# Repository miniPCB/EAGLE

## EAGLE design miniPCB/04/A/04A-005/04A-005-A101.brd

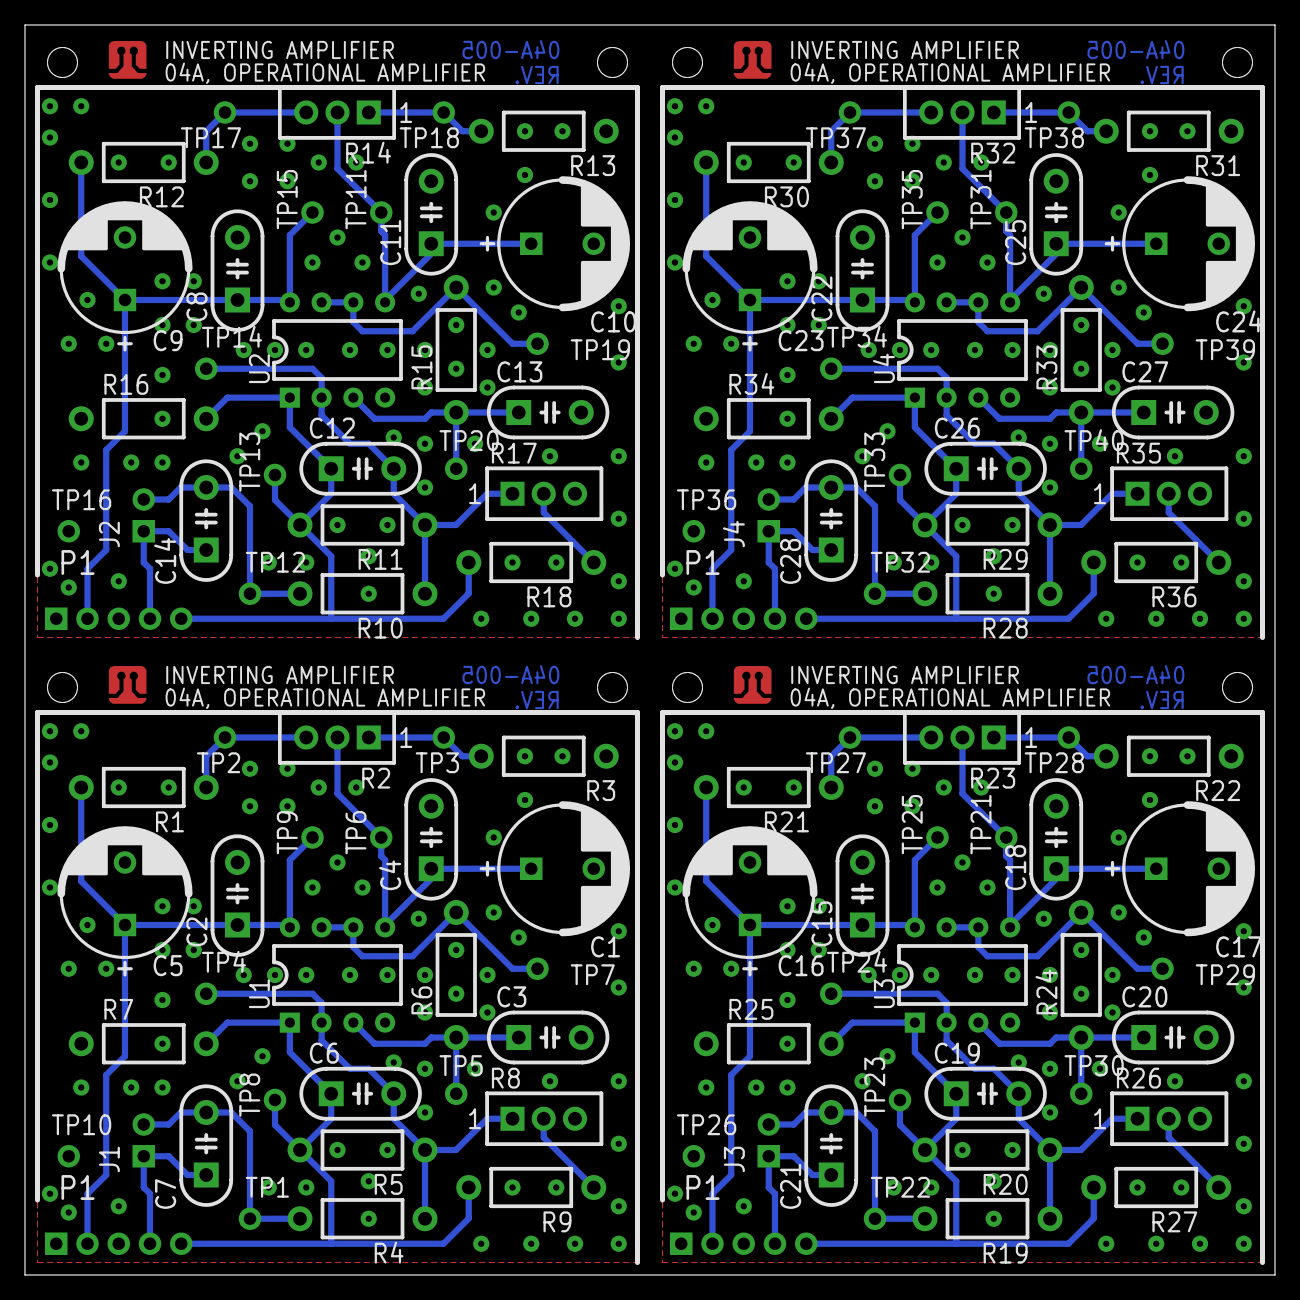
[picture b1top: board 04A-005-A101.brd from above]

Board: 2 copper layers, 100.0 x 100.0 mm, 120 parts (0 on the bottom side), 48 nets.

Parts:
C1, C5, C9, C10, C16, C17, C23, C24: C5MM
C2, C3, C4, C6, C7, C8, C11, C12, C13, C14, C15, C18, C19, C20, C21, C22, C25, C26, C27, C28: C050-024X044
J1, J2, J3, J4: JUMPER; PINS_2
P1, P2, P3, P4: PINS_1X5
R1, R3, R4, R5, R6, R7, R9, R10, R11, R12, R13, R15, R16, R18, R19, R20, R21, R22, R24, R25, R27, R28, R29, R30, R31, R33, R34, R36: 0207/10
R2, R8, R14, R17, R23, R26, R32, R35: TRIM_0100
TP1, TP2, TP3, TP4, TP5, TP6, TP7, TP8, TP9, TP10, TP11, TP12, TP13, TP14, TP15, TP16, TP17, TP18, TP19, TP20, TP21, TP22, TP23, TP24, TP25, TP26, TP27, TP28, TP29, TP30, TP31, TP32, TP33, TP34, TP35, TP36, TP37, TP38, TP39, TP40: PINS_1_TESTPOINT_KE5000_NOTEXT
U1, U2, U3, U4: DIL08
U$1, U$2, U$3, U$4: MINIPCB_50X50; MINIPCB_0P_50X50MM

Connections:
GND: C1.-, C2.2, C3.2, C4.2, C5.-, P1.1, R3.1, R7.1, TP10.1, U1.4
GND1: C8.2, C9.-, C10.-, C11.2, C13.2, P2.1, R13.1, R16.1, TP16.1, U2.4
GND2: C15.2, C16.-, C17.-, C18.2, C20.2, P3.1, R22.1, R25.1, TP26.1, U3.4
GND3: C22.2, C23.-, C24.-, C25.2, C27.2, P4.1, R31.1, R34.1, TP36.1, U4.4
IN: C7.1, J1.1, P1.4
IN1: C14.1, J2.1, P2.4
IN2: C21.1, J3.1, P3.4
IN3: C28.1, J4.1, P4.4
IN-DC: C7.2, J1.2, R4.2, TP1.1
IN-DC1: C14.2, J2.2, R10.2, TP12.1
IN-DC2: C21.2, J3.2, R19.2, TP22.1
IN-DC3: C28.2, J4.2, R28.2, TP32.1
unnamed: R8.2, R9.1
unnamed: R17.2, R18.1
unnamed: R26.2, R27.1
unnamed: R35.2, R36.1
OUT: C6.1, P1.5, R5.2, R7.2, R9.2, TP8.1, U1.1
OUT1: C12.1, P2.5, R11.2, R16.2, R18.2, TP13.1, U2.1
OUT2: C19.1, P3.5, R20.2, R25.2, R27.2, TP23.1, U3.1
OUT3: C26.1, P4.5, R29.2, R34.2, R36.2, TP33.1, U4.1
P1.1: R2.1, R3.2, TP3.1
P1.2: R12.1, R14.3, TP17.1
P1.3: R1.1, R2.3, TP2.1
P1.4: R13.2, R14.1, TP18.1
P1.5: R21.1, R23.3, TP27.1
P1.6: R22.2, R23.1, TP28.1
P1.7: R30.1, R32.3, TP37.1
P1.8: R31.2, R32.1, TP38.1
V+: C2.1, C5.+, P1.2, R1.2, TP9.1, U1.8
V+1: C8.1, C9.+, P2.2, R12.2, TP15.1, U2.8
V+2: C15.1, C16.+, P3.2, R21.2, TP25.1, U3.8
V+3: C22.1, C23.+, P4.2, R30.2, TP35.1, U4.8
VFB: C6.2, R4.1, R5.1, R8.1, TP4.1, U1.2
VFB1: C12.2, R10.1, R11.1, R17.1, TP14.1, U2.2
VFB2: C19.2, R19.1, R20.1, R26.1, TP24.1, U3.2
VFB3: C26.2, R28.1, R29.1, R35.1, TP34.1, U4.2
VR: C1.+, C4.1, R2.2, TP6.1, U1.5
VR1: C10.+, C11.1, R14.2, TP11.1, U2.5
VR2: C17.+, C18.1, R23.2, TP21.1, U3.5
VR3: C24.+, C25.1, R32.2, TP31.1, U4.5
VREF: R6.2, TP7.1, U1.6, U1.7
VREF1: R15.2, TP19.1, U2.6, U2.7
VREF2: R24.2, TP29.1, U3.6, U3.7
VREF3: R33.2, TP39.1, U4.6, U4.7
VREF+: C3.1, R6.1, TP5.1, U1.3
VREF+1: C13.1, R15.1, TP20.1, U2.3
VREF+2: C20.1, R24.1, TP30.1, U3.3
VREF+3: C27.1, R33.1, TP40.1, U4.3

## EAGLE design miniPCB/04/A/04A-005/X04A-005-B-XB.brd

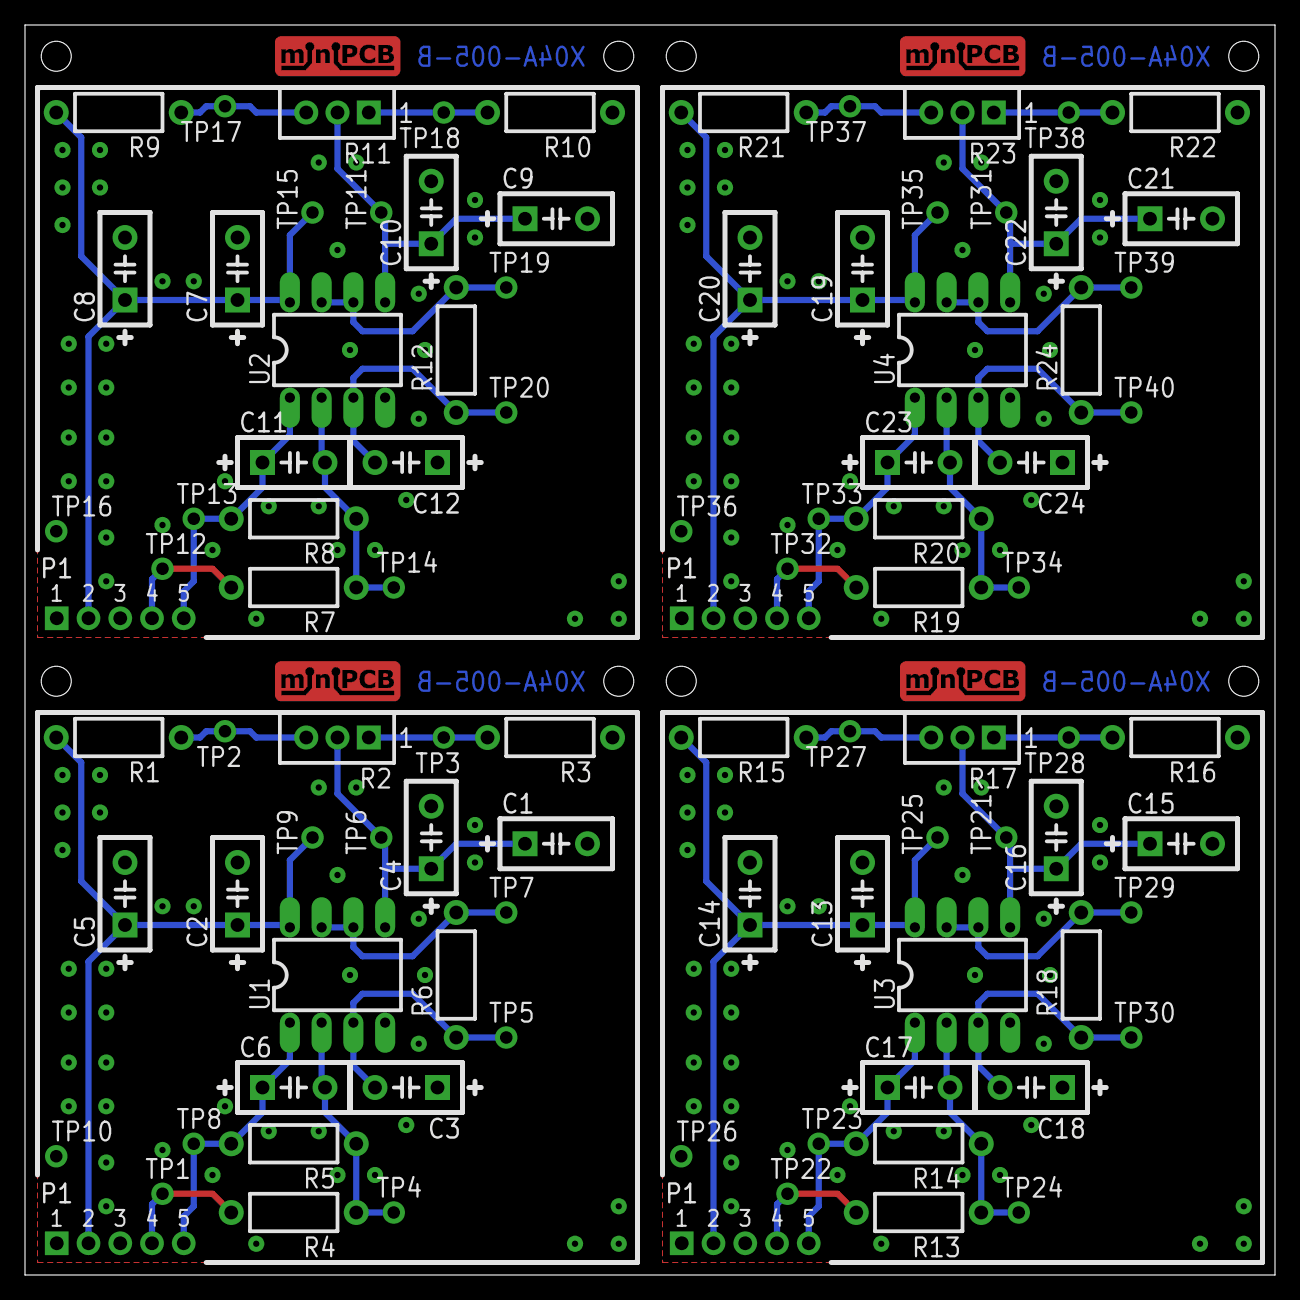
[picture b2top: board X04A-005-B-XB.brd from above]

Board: 2 copper layers, 100.0 x 100.0 mm, 97 parts (0 on the bottom side), 40 nets.

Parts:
C1, C2, C3, C4, C5, C6, C7, C8, C9, C10, C11, C12, C13, C14, C15, C16, C17, C18, C19, C20, C21, C22, C23, C24: C050-024X044
E$1: MINIPCB_PANEL_IMAGEFRAME
P1-, P1-1, P1-2, P1-3: MINIPCB_5P_50X50MM
R1, R3, R4, R5, R6, R7, R8, R9, R10, R12, R13, R14, R15, R16, R18, R19, R20, R21, R22, R24: 0207/10
R2, R11, R17, R23: TRIM_0100
TP1, TP2, TP3, TP4, TP5, TP6, TP7, TP8, TP9, TP10, TP11, TP12, TP13, TP14, TP15, TP16, TP17, TP18, TP19, TP20, TP21, TP22, TP23, TP24, TP25, TP26, TP27, TP28, TP29, TP30, TP31, TP32, TP33, TP34, TP35, TP36, TP37, TP38, TP39, TP40: PINS_1_TESTPOINT_KE5000_NOTEXT
U1, U2, U3, U4: DIL08

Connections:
GND: C1.2, C2.2, C3.1, C4.2, C5.2, P1-.1, R3.1, TP10.1, U1.4
GND1: C7.2, C8.2, C9.2, C10.2, C12.1, P1-1.1, R10.1, TP16.1, U2.4
GND2: C13.2, C14.2, C15.2, C16.2, C18.1, P1-2.1, R16.1, TP26.1, U3.4
GND3: C19.2, C20.2, C21.2, C22.2, C24.1, P1-3.1, R22.1, TP36.1, U4.4
IN: P1-.4, R4.2, TP1.1
IN1: P1-1.4, R7.2, TP12.1
IN2: P1-2.4, R13.2, TP22.1
IN3: P1-3.4, R19.2, TP32.1
unnamed: C1.1, C4.1, R2.2, TP6.1, U1.5
unnamed: C3.2, R6.1, TP5.1, U1.3
unnamed: C9.1, C10.1, R11.2, TP11.1, U2.5
unnamed: C12.2, R12.1, TP20.1, U2.3
unnamed: C15.1, C16.1, R17.2, TP21.1, U3.5
unnamed: C18.2, R18.1, TP30.1, U3.3
unnamed: C21.1, C22.1, R23.2, TP31.1, U4.5
unnamed: C24.2, R24.1, TP40.1, U4.3
OUT: C6.1, P1-.5, R5.2, TP8.1, U1.1
OUT1: C11.1, P1-1.5, R8.2, TP13.1, U2.1
OUT2: C17.1, P1-2.5, R14.2, TP23.1, U3.1
OUT3: C23.1, P1-3.5, R20.2, TP33.1, U4.1
P1.1: R2.1, R3.2, TP3.1
P1.2: R9.1, R11.3, TP17.1
P1.3: R1.1, R2.3, TP2.1
P1.4: R10.2, R11.1, TP18.1
P1.5: R15.1, R17.3, TP27.1
P1.6: R16.2, R17.1, TP28.1
P1.7: R21.1, R23.3, TP37.1
P1.8: R22.2, R23.1, TP38.1
V+: C2.1, C5.1, P1-.2, R1.2, TP9.1, U1.8
V+1: C7.1, C8.1, P1-1.2, R9.2, TP15.1, U2.8
V+2: C13.1, C14.1, P1-2.2, R15.2, TP25.1, U3.8
V+3: C19.1, C20.1, P1-3.2, R21.2, TP35.1, U4.8
VFB: C6.2, R4.1, R5.1, TP4.1, U1.2
VFB1: C11.2, R7.1, R8.1, TP14.1, U2.2
VFB2: C17.2, R13.1, R14.1, TP24.1, U3.2
VFB3: C23.2, R19.1, R20.1, TP34.1, U4.2
VREF: R6.2, TP7.1, U1.6, U1.7
VREF1: R12.2, TP19.1, U2.6, U2.7
VREF2: R18.2, TP29.1, U3.6, U3.7
VREF3: R24.2, TP39.1, U4.6, U4.7

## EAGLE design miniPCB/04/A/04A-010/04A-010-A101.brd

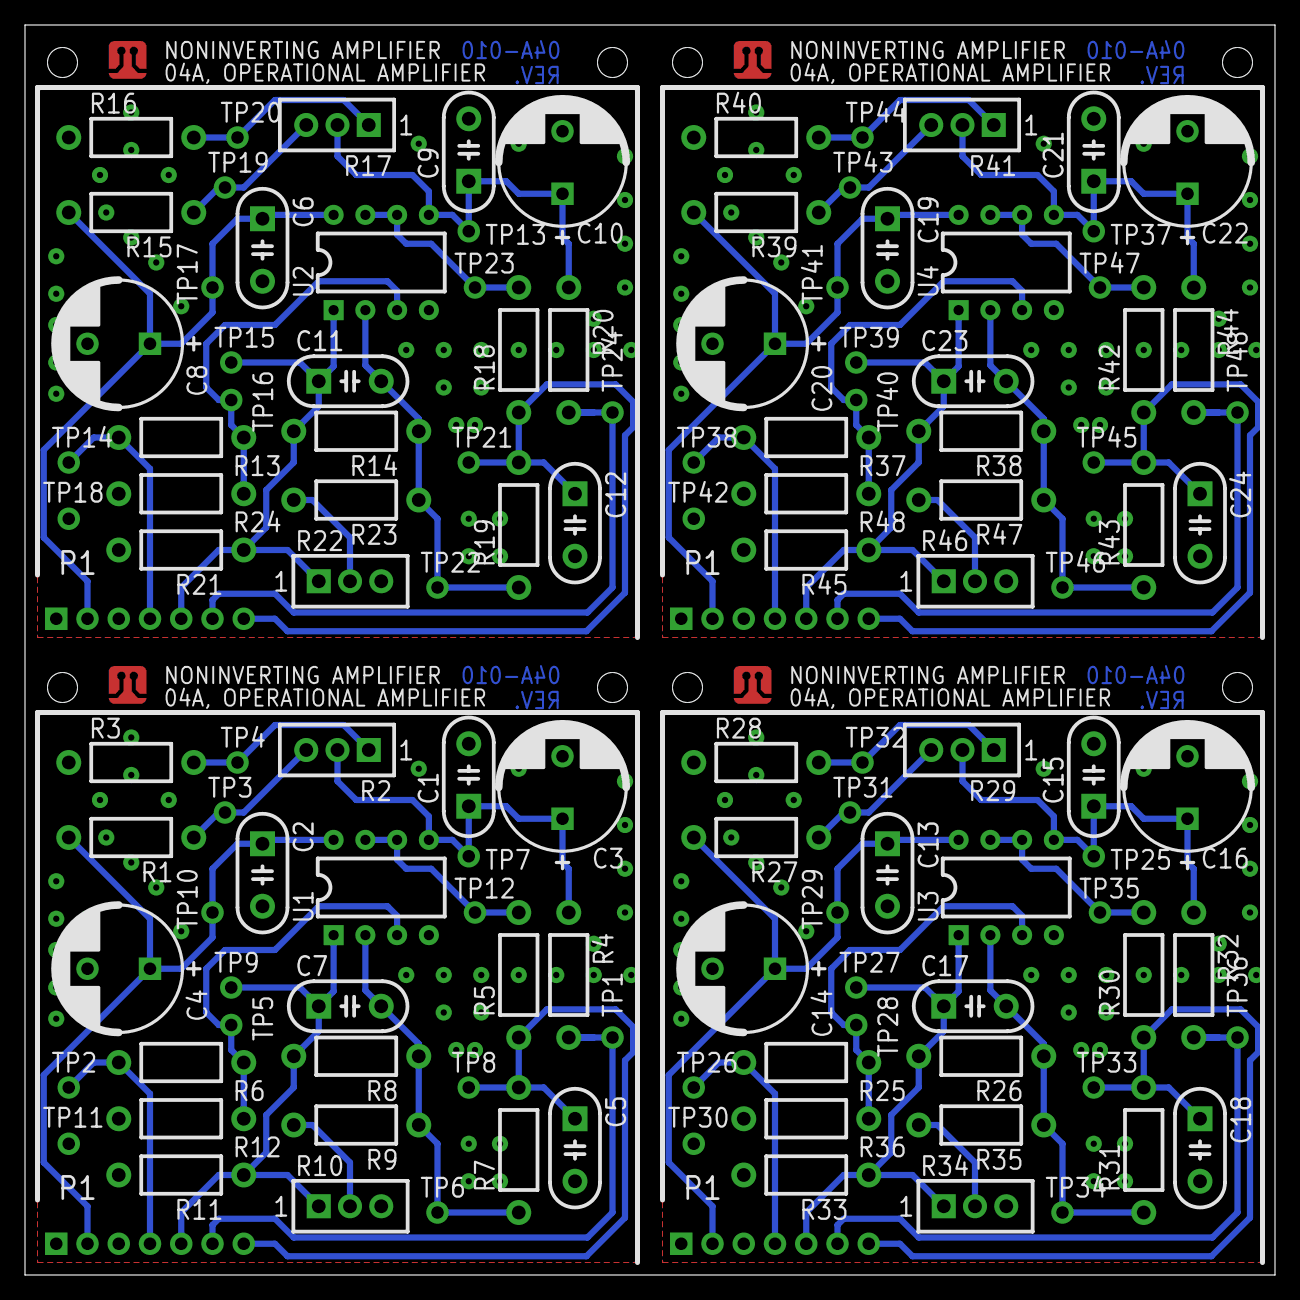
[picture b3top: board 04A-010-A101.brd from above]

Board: 2 copper layers, 100.0 x 100.0 mm, 133 parts (0 on the bottom side), 52 nets.

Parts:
C1, C2, C5, C6, C7, C9, C11, C12, C13, C15, C17, C18, C19, C21, C23, C24: C050-024X044
C3, C4, C8, C10, C14, C16, C20, C22: C5MM
E$1: MINIPCB_PANEL_IMAGEFRAME
P1, P2, P3, P4: PINS_1X7
R1, R3, R4, R5, R6, R7, R8, R9, R11, R12, R13, R14, R15, R16, R18, R19, R20, R21, R23, R24, R25, R26, R27, R28, R30, R31, R32, R33, R35, R36, R37, R38, R39, R40, R42, R43, R44, R45, R47, R48: 0207/10
R2, R10, R17, R22, R29, R34, R41, R46: TRIM_0100
TP1, TP2, TP3, TP4, TP5, TP6, TP7, TP8, TP9, TP10, TP11, TP12, TP13, TP14, TP15, TP16, TP17, TP18, TP19, TP20, TP21, TP22, TP23, TP24, TP25, TP26, TP27, TP28, TP29, TP30, TP31, TP32, TP33, TP34, TP35, TP36, TP37, TP38, TP39, TP40, TP41, TP42, TP43, TP44, TP45, TP46, TP47, TP48: PINS_1_TESTPOINT_KE5000_NOTEXT
U1, U2, U3, U4: DIL08
U$1, U$2, U$3, U$4: MINIPCB_50X50; MINIPCB_0P_50X50MM

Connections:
BIAS: C1.1, C3.+, R2.2, R4.1, TP7.1, U1.5
BIAS1: C9.1, C10.+, R17.2, R20.1, TP13.1, U2.5
BIAS2: C15.1, C16.+, R29.2, R32.1, TP25.1, U3.5
BIAS3: C21.1, C22.+, R41.2, R44.1, TP37.1, U4.5
BIAS_CONTROL: P1.6, R4.2, TP1.1
BIAS_CONTROL1: P2.6, R20.2, TP24.1
BIAS_CONTROL2: P3.6, R32.2, TP36.1
BIAS_CONTROL3: P4.6, R44.2, TP48.1
GND: C1.2, C2.2, C3.-, C4.-, C5.2, P1.1, R3.1, R11.2, R12.2, TP11.1, U1.4
GND1: C6.2, C8.-, C9.2, C10.-, C12.2, P2.1, R16.1, R21.2, R24.2, TP18.1, U2.4
GND2: C13.2, C14.-, C15.2, C16.-, C18.2, P3.1, R28.1, R33.2, R36.2, TP30.1, U3.4
GND3: C19.2, C20.-, C21.2, C22.-, C24.2, P4.1, R40.1, R45.2, R48.2, TP42.1, U4.4
IN: P1.4, R6.2, TP2.1
IN1: P2.4, R13.2, TP14.1
IN2: P3.4, R25.2, TP26.1
IN3: P4.4, R37.2, TP38.1
IN+: R6.1, R12.1, TP5.1, U1.3
IN+1: R13.1, R24.1, TP16.1, U2.3
IN+2: R25.1, R36.1, TP28.1, U3.3
IN+3: R37.1, R48.1, TP40.1, U4.3
unnamed: R9.2, R10.2
unnamed: R22.2, R23.2
unnamed: R34.2, R35.2
unnamed: R46.2, R47.2
OUT: C7.1, P1.5, R8.2, R10.1, R11.1, TP9.1, U1.1
OUT1: C11.1, P2.5, R14.2, R21.1, R22.1, TP15.1, U2.1
OUT2: C17.1, P3.5, R26.2, R33.1, R34.1, TP27.1, U3.1
OUT3: C23.1, P4.5, R38.2, R45.1, R46.1, TP39.1, U4.1
POT.1: R2.1, R3.2, TP4.1
POT.2: R15.1, R17.3, TP19.1
POT.3: R1.1, R2.3, TP3.1
POT.4: R16.2, R17.1, TP20.1
POT.5: R27.1, R29.3, TP31.1
POT.6: R28.2, R29.1, TP32.1
POT.7: R39.1, R41.3, TP43.1
POT.8: R40.2, R41.1, TP44.1
V+: C2.1, C4.+, P1.2, R1.2, TP10.1, U1.8
V+1: C6.1, C8.+, P2.2, R15.2, TP17.1, U2.8
V+2: C13.1, C14.+, P3.2, R27.2, TP29.1, U3.8
V+3: C19.1, C20.+, P4.2, R39.2, TP41.1, U4.8
VFB: C7.2, R7.1, R8.1, R9.1, TP6.1, U1.2
VFB1: C11.2, R14.1, R19.1, R23.1, TP22.1, U2.2
VFB2: C17.2, R26.1, R31.1, R35.1, TP34.1, U3.2
VFB3: C23.2, R38.1, R43.1, R47.1, TP46.1, U4.2
VREF: R5.2, TP12.1, U1.6, U1.7
VREF1: R18.2, TP23.1, U2.6, U2.7
VREF2: R30.2, TP35.1, U3.6, U3.7
VREF3: R42.2, TP47.1, U4.6, U4.7
VREF_FILTERED: C5.1, P1.7, R5.1, R7.2, TP8.1
VREF_FILTERED1: C12.1, P2.7, R18.1, R19.2, TP21.1
VREF_FILTERED2: C18.1, P3.7, R30.1, R31.2, TP33.1
VREF_FILTERED3: C24.1, P4.7, R42.1, R43.2, TP45.1

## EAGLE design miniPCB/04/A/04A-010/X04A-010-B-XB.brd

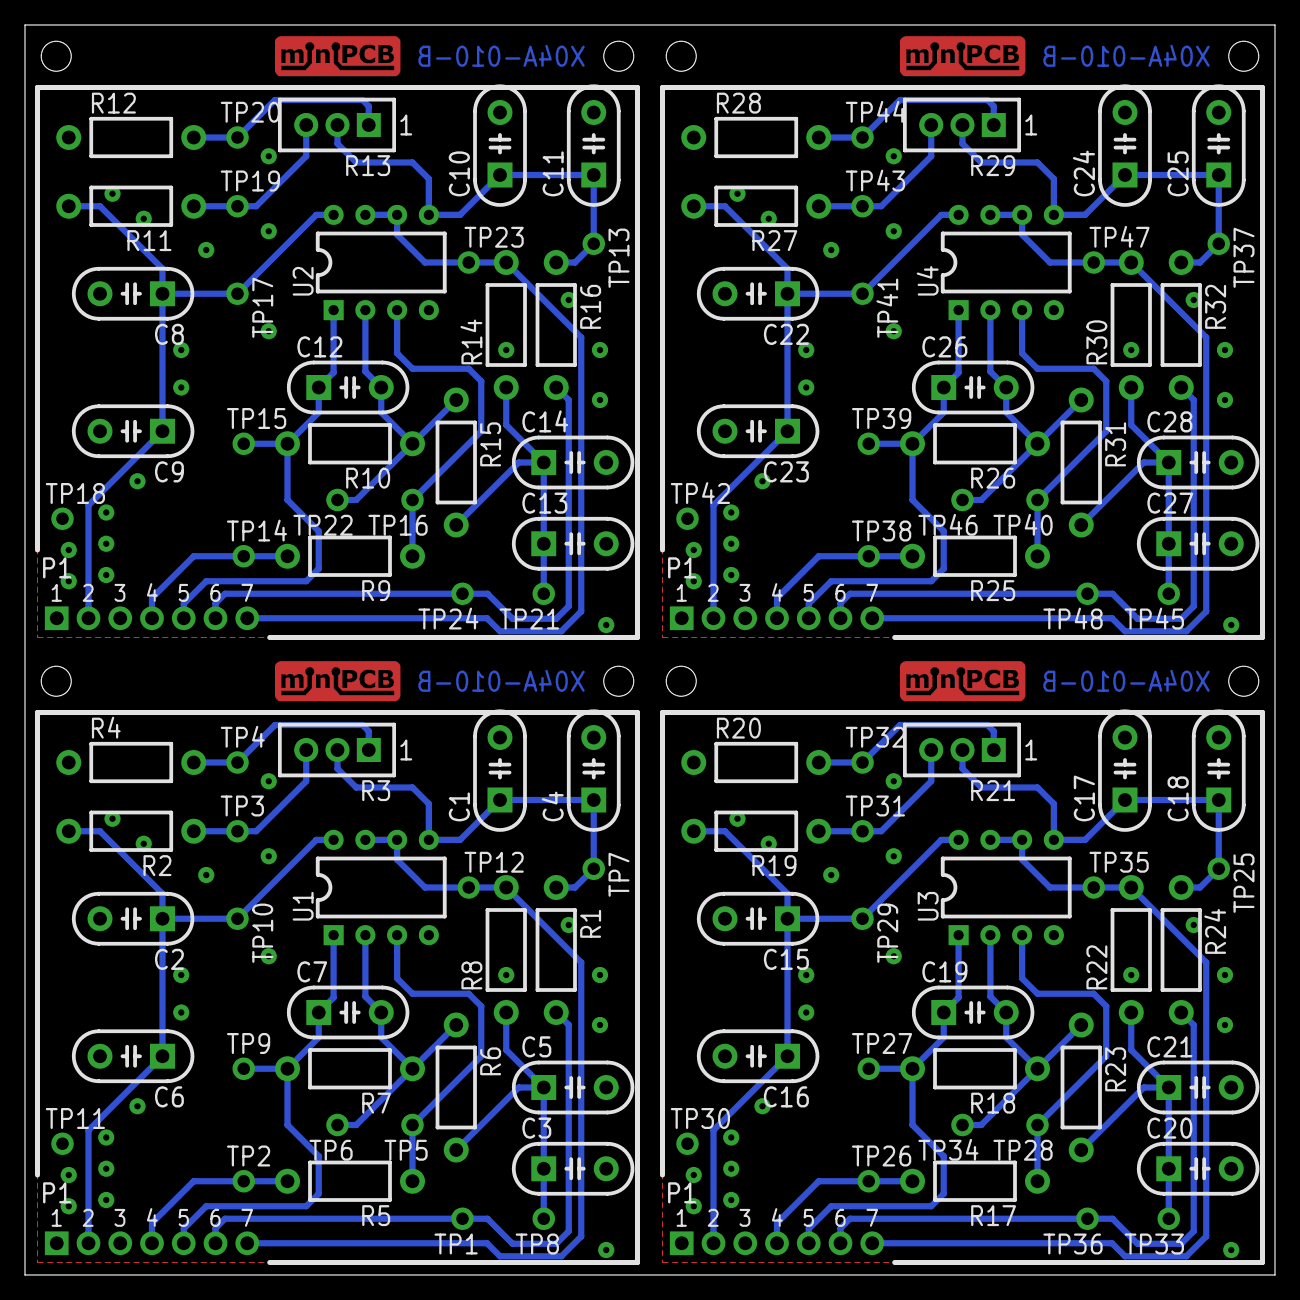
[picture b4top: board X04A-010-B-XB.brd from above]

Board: 2 copper layers, 100.0 x 100.0 mm, 117 parts (0 on the bottom side), 48 nets.

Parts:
C1, C2, C3, C4, C5, C6, C7, C8, C9, C10, C11, C12, C13, C14, C15, C16, C17, C18, C19, C20, C21, C22, C23, C24, C25, C26, C27, C28: C050-024X044
E$1: MINIPCB_PANEL_IMAGEFRAME
P1-, P1-1, P1-2, P1-3: MINIPCB_7P_50X50
R1, R2, R4, R5, R6, R7, R8, R9, R10, R11, R12, R14, R15, R16, R17, R18, R19, R20, R22, R23, R24, R25, R26, R27, R28, R30, R31, R32: 0207/10
R3, R13, R21, R29: TRIM_0100
TP1, TP2, TP3, TP4, TP5, TP6, TP7, TP8, TP9, TP10, TP11, TP12, TP13, TP14, TP15, TP16, TP17, TP18, TP19, TP20, TP21, TP22, TP23, TP24, TP25, TP26, TP27, TP28, TP29, TP30, TP31, TP32, TP33, TP34, TP35, TP36, TP37, TP38, TP39, TP40, TP41, TP42, TP43, TP44, TP45, TP46, TP47, TP48: PINS_1_TESTPOINT_KE5000_NOTEXT
U1, U2, U3, U4: DIL08

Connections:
BIAS: C1.1, C4.1, R1.1, R3.2, TP7.1, U1.5
BIAS1: C10.1, C11.1, R13.2, R16.1, TP13.1, U2.5
BIAS2: C17.1, C18.1, R21.2, R24.1, TP25.1, U3.5
BIAS3: C24.1, C25.1, R29.2, R32.1, TP37.1, U4.5
BIAS_CONTROL: P1-.6, R1.2, TP1.1
BIAS_CONTROL1: P1-1.6, R16.2, TP24.1
BIAS_CONTROL2: P1-2.6, R24.2, TP36.1
BIAS_CONTROL3: P1-3.6, R32.2, TP48.1
GND: C1.2, C2.2, C3.2, C4.2, C5.2, C6.2, P1-.1, R4.1, TP11.1, U1.4
GND1: C8.2, C9.2, C10.2, C11.2, C13.2, C14.2, P1-1.1, R12.1, TP18.1, U2.4
GND2: C15.2, C16.2, C17.2, C18.2, C20.2, C21.2, P1-2.1, R20.1, TP30.1, U3.4
GND3: C22.2, C23.2, C24.2, C25.2, C27.2, C28.2, P1-3.1, R28.1, TP42.1, U4.4
IN: P1-.4, R5.2, TP2.1
IN1: P1-1.4, R9.2, TP14.1
IN2: P1-2.4, R17.2, TP26.1
IN3: P1-3.4, R25.2, TP38.1
IN+: R5.1, TP5.1, U1.3
IN+1: R9.1, TP16.1, U2.3
IN+2: R17.1, TP28.1, U3.3
IN+3: R25.1, TP40.1, U4.3
OUT: C7.1, P1-.5, R7.2, TP9.1, U1.1
OUT1: C12.1, P1-1.5, R10.2, TP15.1, U2.1
OUT2: C19.1, P1-2.5, R18.2, TP27.1, U3.1
OUT3: C26.1, P1-3.5, R26.2, TP39.1, U4.1
POT.1: R3.1, R4.2, TP4.1
POT.2: R11.1, R13.3, TP19.1
POT.3: R2.1, R3.3, TP3.1
POT.4: R12.2, R13.1, TP20.1
POT.5: R19.1, R21.3, TP31.1
POT.6: R20.2, R21.1, TP32.1
POT.7: R27.1, R29.3, TP43.1
POT.8: R28.2, R29.1, TP44.1
V+: C2.1, C6.1, P1-.2, R2.2, TP10.1, U1.8
V+1: C8.1, C9.1, P1-1.2, R11.2, TP17.1, U2.8
V+2: C15.1, C16.1, P1-2.2, R19.2, TP29.1, U3.8
V+3: C22.1, C23.1, P1-3.2, R27.2, TP41.1, U4.8
VFB: C7.2, R6.1, R7.1, TP6.1, U1.2
VFB1: C12.2, R10.1, R15.1, TP22.1, U2.2
VFB2: C19.2, R18.1, R23.1, TP34.1, U3.2
VFB3: C26.2, R26.1, R31.1, TP46.1, U4.2
VREF: P1-.7, R8.2, TP12.1, U1.6, U1.7
VREF1: P1-1.7, R14.2, TP23.1, U2.6, U2.7
VREF2: P1-2.7, R22.2, TP35.1, U3.6, U3.7
VREF3: P1-3.7, R30.2, TP47.1, U4.6, U4.7
VREF_FILTERED: C3.1, C5.1, R6.2, R8.1, TP8.1
VREF_FILTERED1: C13.1, C14.1, R14.1, R15.2, TP21.1
VREF_FILTERED2: C20.1, C21.1, R22.1, R23.2, TP33.1
VREF_FILTERED3: C27.1, C28.1, R30.1, R31.2, TP45.1
